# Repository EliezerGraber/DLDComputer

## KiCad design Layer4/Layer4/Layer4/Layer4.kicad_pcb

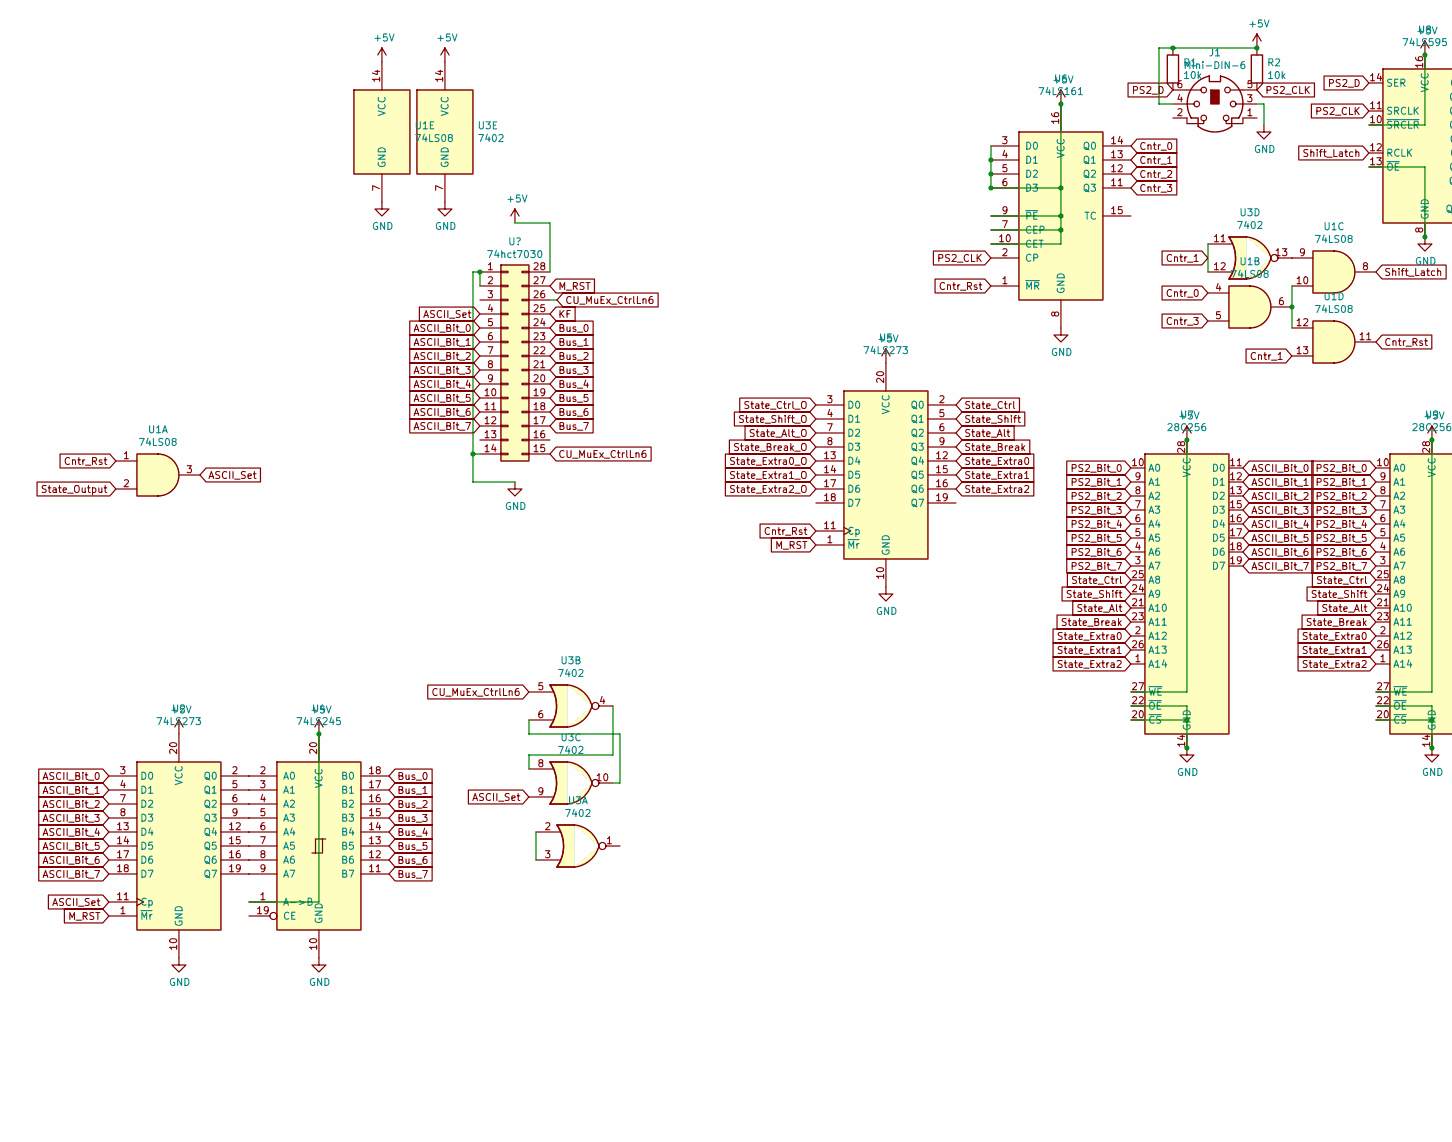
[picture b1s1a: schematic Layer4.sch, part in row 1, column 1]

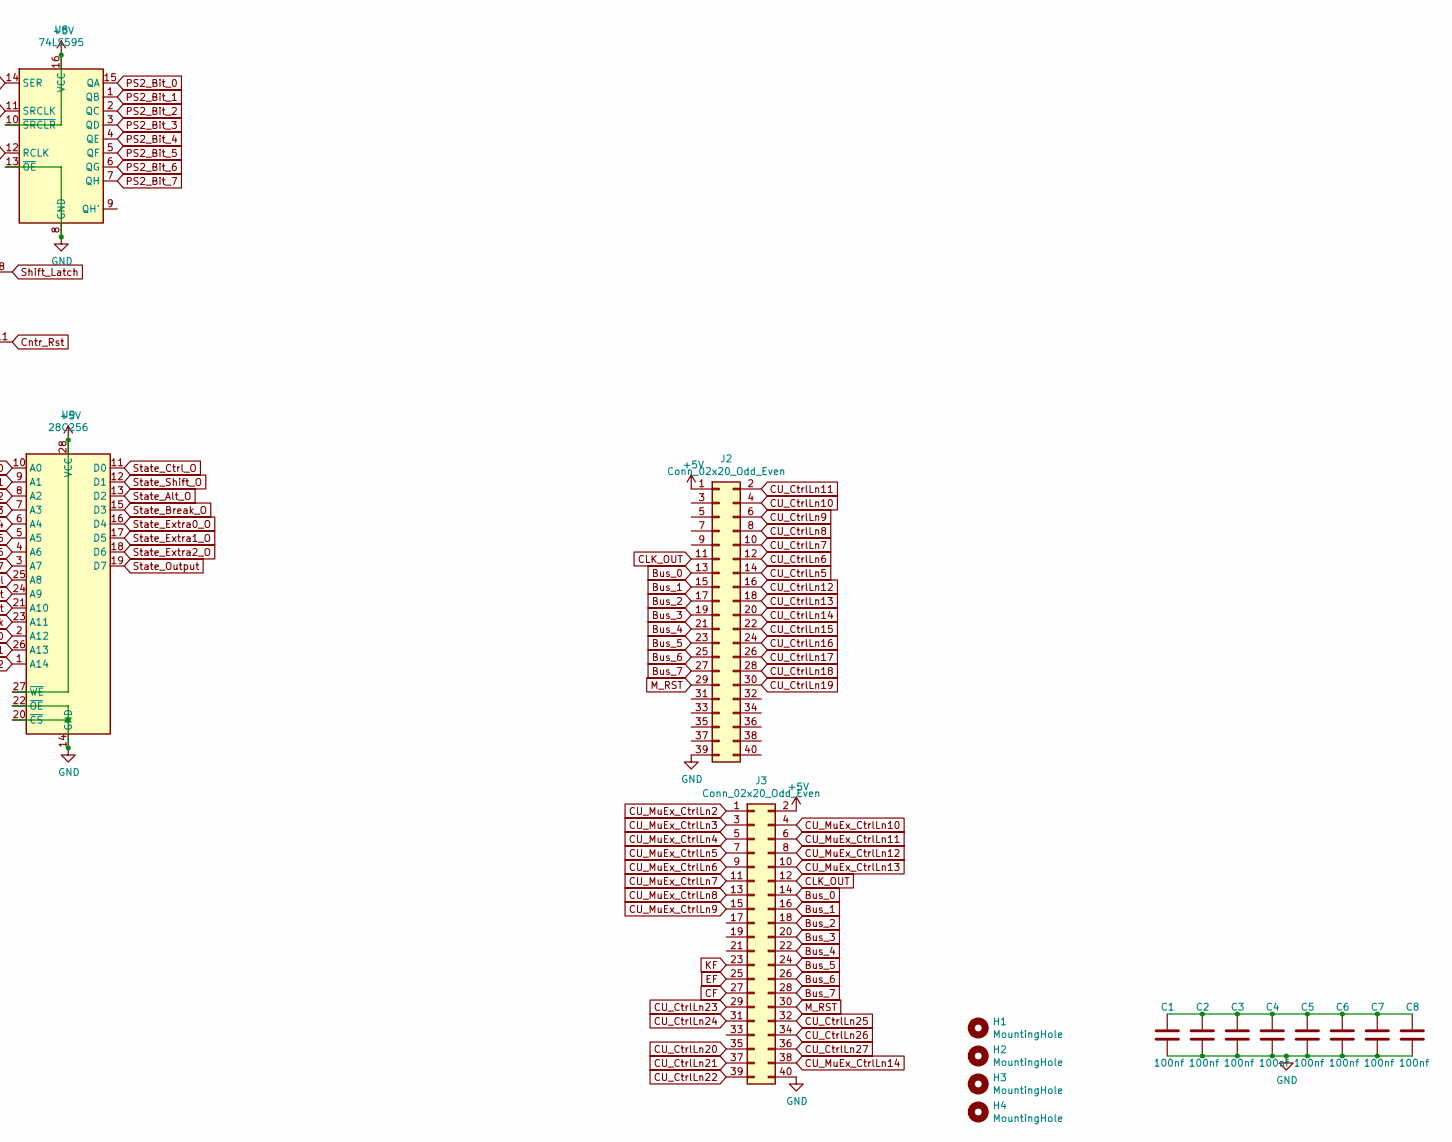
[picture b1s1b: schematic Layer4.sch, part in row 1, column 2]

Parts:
C1, C2, C3, C4, C5, C6, C7, C8: 100nf; C_Disc_D5.0mm_W2.5mm_P2.50mm
H1, H2, H3, H4: MountingHole; MountingHole_4mm
J1: Mini-DIN-6; Connector_Mini-DIN_Female_6Pin_2rows
J2, J3: Conn_02x20_Odd_Even; PinHeader_2x20_P2.54mm_Vertical
R1, R2: 10k; R_Axial_DIN0309_L9.0mm_D3.2mm_P12.70mm_Horizontal
U1: 74LS08; DIP-14_W7.62mm_LongPads
U2, U5: 74LS273; DIP-20_W7.62mm_LongPads
U3: 7402; DIP-14_W7.62mm_LongPads
U4: 74LS245; DIP-20_W7.62mm_LongPads
U6: 74LS161; DIP-16_W7.62mm_LongPads
U7, U9: 28C256; DIP-28_W15.24mm_LongPads
U8: 74LS595; DIP-16_W7.62mm_LongPads

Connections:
+5V: J1.4, J2.1, J3.2, R1.1, R2.1, U1.14 (VCC), U2.20 (VCC), U3.14 (VCC), U4.1 (A->B), U4.20 (VCC), U5.20 (VCC), U6.3 (D0), U6.4 (D1), U6.5 (D2), U6.6 (D3), U6.7 (CEP), U6.9 (~PE), U6.10 (CET), U6.16 (VCC), U7.27 (~WE), U7.28 (VCC), U8.10 (~SRCLR), U8.16 (VCC), U9.27 (~WE), U9.28 (VCC)
ASCII_Bit_0: U2.3 (D0), U7.11 (D0)
ASCII_Bit_1: U2.4 (D1), U7.12 (D1)
ASCII_Bit_2: U2.7 (D2), U7.13 (D2)
ASCII_Bit_3: U2.8 (D3), U7.15 (D3)
ASCII_Bit_4: U2.13 (D4), U7.16 (D4)
ASCII_Bit_5: U2.14 (D5), U7.17 (D5)
ASCII_Bit_6: U2.17 (D6), U7.18 (D6)
ASCII_Bit_7: U2.18 (D7), U7.19 (D7)
ASCII_Set: U1.3, U2.11 (Cp), U3.9
Bus_0: J2.13, J3.14, U4.18 (B0)
Bus_1: J2.15, J3.16, U4.17 (B1)
Bus_2: J2.17, J3.18, U4.16 (B2)
Bus_3: J2.19, J3.20, U4.15 (B3)
Bus_4: J2.21, J3.22, U4.14 (B4)
Bus_5: J2.23, J3.24, U4.13 (B5)
Bus_6: J2.25, J3.26, U4.12 (B6)
Bus_7: J2.27, J3.28, U4.11 (B7)
CF: J3.27
CLK_OUT: J2.11, J3.12
CU_CtrlLn5: J2.14
CU_CtrlLn6: J2.12
CU_CtrlLn7: J2.10
CU_CtrlLn8: J2.8
CU_CtrlLn9: J2.6
CU_CtrlLn10: J2.4
CU_CtrlLn11: J2.2
CU_CtrlLn12: J2.16
CU_CtrlLn13: J2.18
CU_CtrlLn14: J2.20
CU_CtrlLn15: J2.22
CU_CtrlLn16: J2.24
CU_CtrlLn17: J2.26
CU_CtrlLn18: J2.28
CU_CtrlLn19: J2.30
CU_CtrlLn20: J3.35
CU_CtrlLn21: J3.37
CU_CtrlLn22: J3.39
CU_CtrlLn23: J3.29
CU_CtrlLn24: J3.31
CU_CtrlLn25: J3.32
CU_CtrlLn26: J3.34
CU_CtrlLn27: J3.36
CU_MuEx_CtrlLn2: J3.1
CU_MuEx_CtrlLn3: J3.3
CU_MuEx_CtrlLn4: J3.5
CU_MuEx_CtrlLn5: J3.7
CU_MuEx_CtrlLn7: J3.11
CU_MuEx_CtrlLn8: J3.13
CU_MuEx_CtrlLn9: J3.15
CU_MuEx_CtrlLn10: J3.4
CU_MuEx_CtrlLn11: J3.6
CU_MuEx_CtrlLn12: J3.8
CU_MuEx_CtrlLn13: J3.10
CU_MuEx_CtrlLn14: J3.38
Cntr_0: U1.4, U6.14 (Q0)
Cntr_1: U1.13, U3.11, U3.12, U6.13 (Q1)
Cntr_2: U6.12 (Q2)
Cntr_3: U1.5, U6.11 (Q3)
Cntr_Rst: U1.1, U1.11, U5.11 (Cp), U6.1 (~MR)
EF: J3.25
GND: C1.2, C2.2, C3.2, C4.2, C5.2, C6.2, C7.2, C8.2, J1.3, J2.39, J3.40, U1.7 (GND), U2.10 (GND), U3.7 (GND), U4.10 (GND), U5.10 (GND), U6.8 (GND), U7.14 (GND), U7.20 (~CS), U7.22 (~OE), U8.8 (GND), U8.13 (~OE), U9.14 (GND), U9.20 (~CS), U9.22 (~OE)
M_RST: J2.29, J3.30, U2.1 (~Mr), U5.1 (~Mr)
unnamed: C1.1, C2.1, C3.1, C4.1, C5.1, C6.1, C7.1, C8.1
unnamed: U1.9, U3.13
unnamed: U1.6, U1.10, U1.12
unnamed: U2.2 (Q0), U4.2 (A0)
unnamed: U2.5 (Q1), U4.3 (A1)
unnamed: U2.6 (Q2), U4.4 (A2)
unnamed: U2.9 (Q3), U4.5 (A3)
unnamed: U2.12 (Q4), U4.6 (A4)
unnamed: U2.15 (Q5), U4.7 (A5)
unnamed: U2.16 (Q6), U4.8 (A6)
unnamed: U2.19 (Q7), U4.9 (A7)
unnamed: U3.1, U4.19 (CE)
unnamed: U3.6, U3.10
PS2_Bit_0: U7.10 (A0), U8.15 (QA), U9.10 (A0)
PS2_Bit_1: U7.9 (A1), U8.1 (QB), U9.9 (A1)
PS2_Bit_2: U7.8 (A2), U8.2 (QC), U9.8 (A2)
PS2_Bit_3: U7.7 (A3), U8.3 (QD), U9.7 (A3)
PS2_Bit_4: U7.6 (A4), U8.4 (QE), U9.6 (A4)
PS2_Bit_5: U7.5 (A5), U8.5 (QF), U9.5 (A5)
PS2_Bit_6: U7.4 (A6), U8.6 (QG), U9.4 (A6)
PS2_Bit_7: U7.3 (A7), U8.7 (QH), U9.3 (A7)
PS2_CLK: J1.5, R2.2, U6.2 (CP), U8.11 (SRCLK)
PS2_D: J1.6, R1.2, U8.14 (SER)
Shift_Latch: U1.8, U8.12 (RCLK)
State_Alt: U5.6 (Q2), U7.21 (A10), U9.21 (A10)
State_Alt_O: U5.7 (D2), U9.13 (D2)
State_Break: U5.9 (Q3), U7.23 (A11), U9.23 (A11)
State_Break_O: U5.8 (D3), U9.15 (D3)
State_Ctrl: U5.2 (Q0), U7.25 (A8), U9.25 (A8)
State_Ctrl_O: U5.3 (D0), U9.11 (D0)
State_Extra0: U5.12 (Q4), U7.2 (A12), U9.2 (A12)
State_Extra0_O: U5.13 (D4), U9.16 (D4)
State_Extra1: U5.15 (Q5), U7.26 (A13), U9.26 (A13)
State_Extra1_O: U5.14 (D5), U9.17 (D5)
State_Extra2: U5.16 (Q6), U7.1 (A14), U9.1 (A14)
State_Extra2_O: U5.17 (D6), U9.18 (D6)
State_Output: U1.2, U9.19 (D7)
State_Shift: U5.5 (Q1), U7.24 (A9), U9.24 (A9)
State_Shift_O: U5.4 (D1), U9.12 (D1)

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
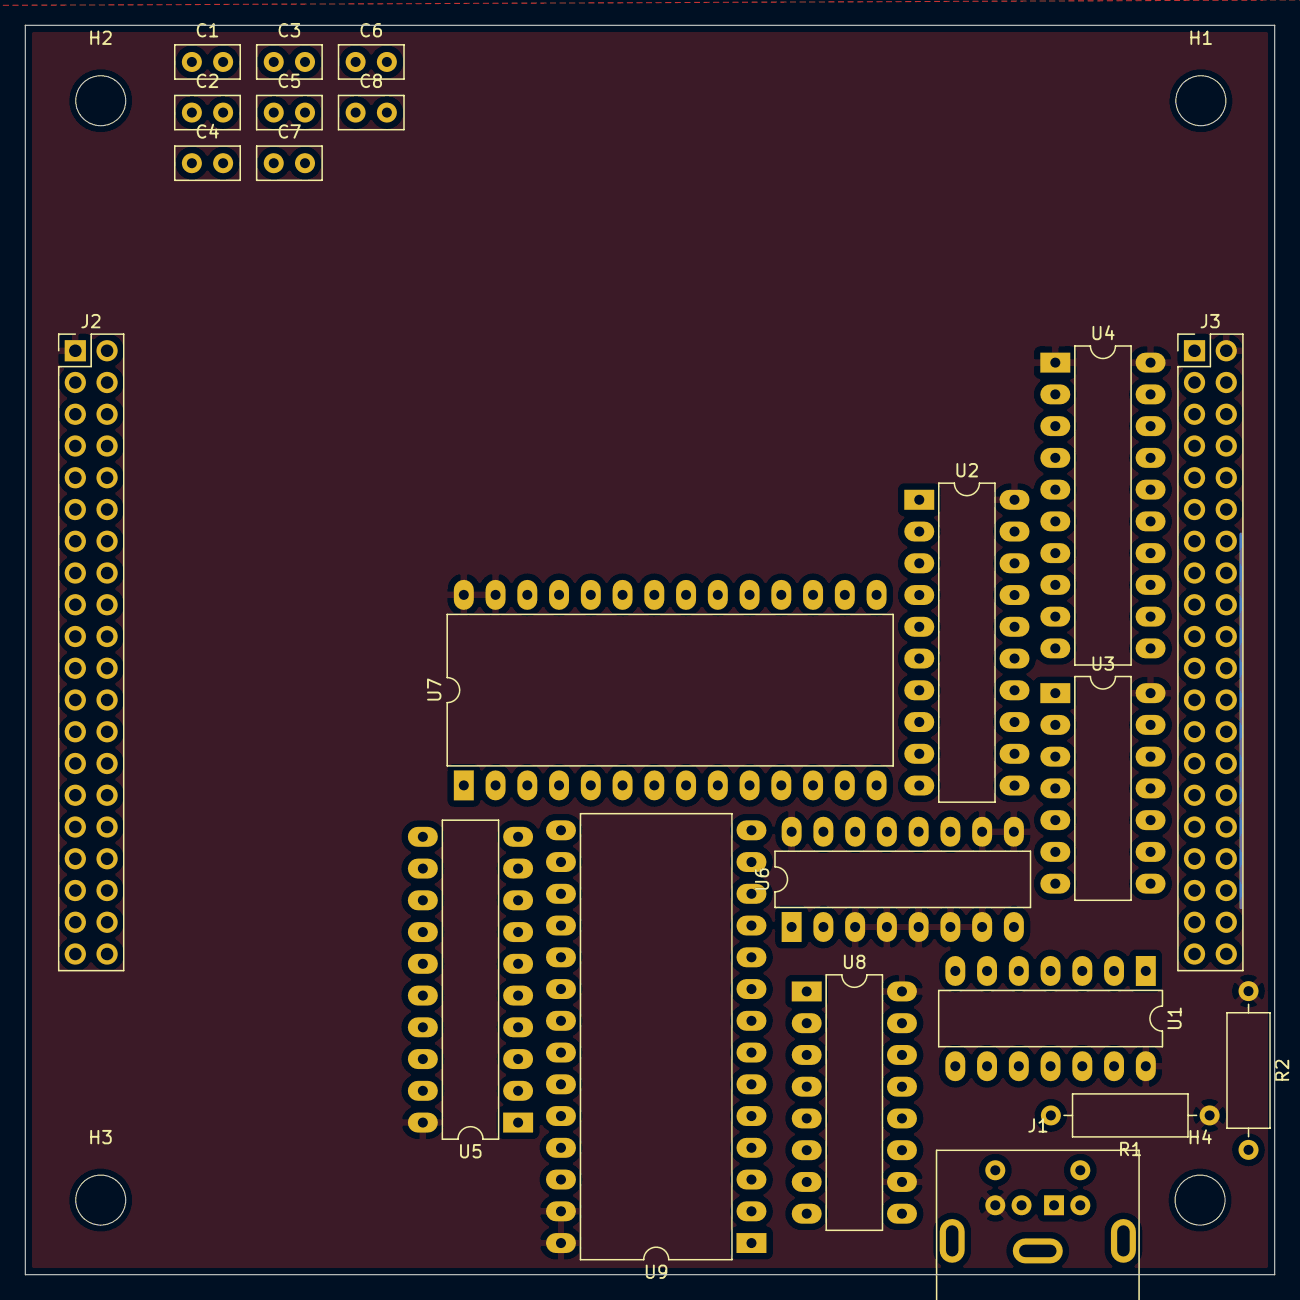
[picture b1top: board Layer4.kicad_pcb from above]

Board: 2 copper layers, 99.9 x 99.9 mm, 26 parts (0 on the bottom side), 66 nets.

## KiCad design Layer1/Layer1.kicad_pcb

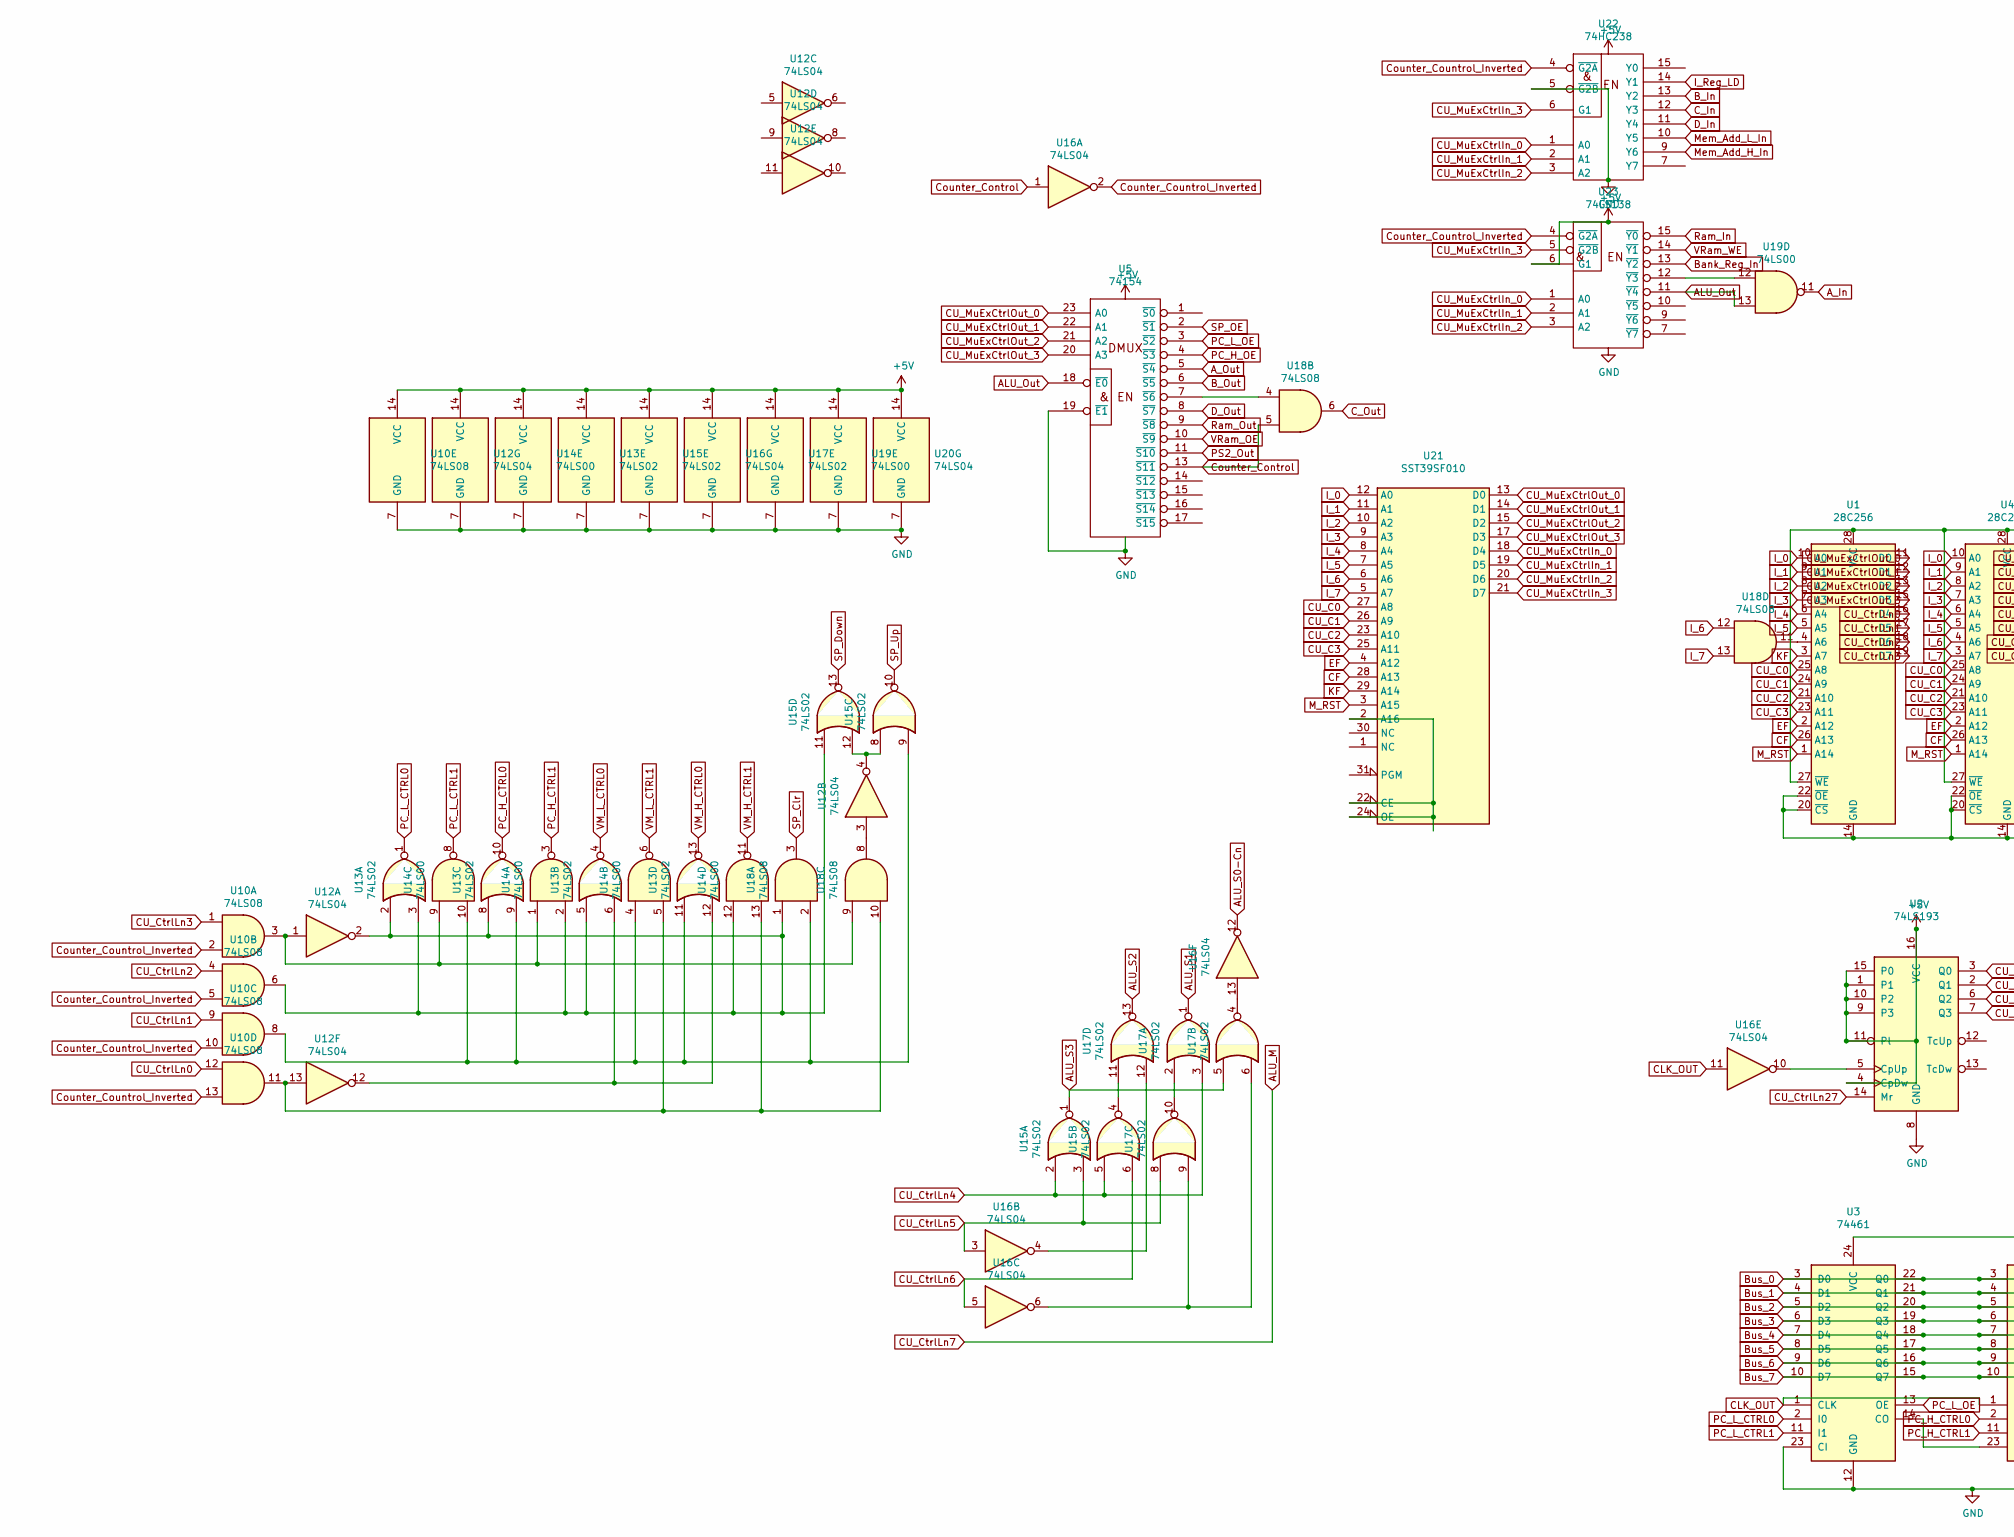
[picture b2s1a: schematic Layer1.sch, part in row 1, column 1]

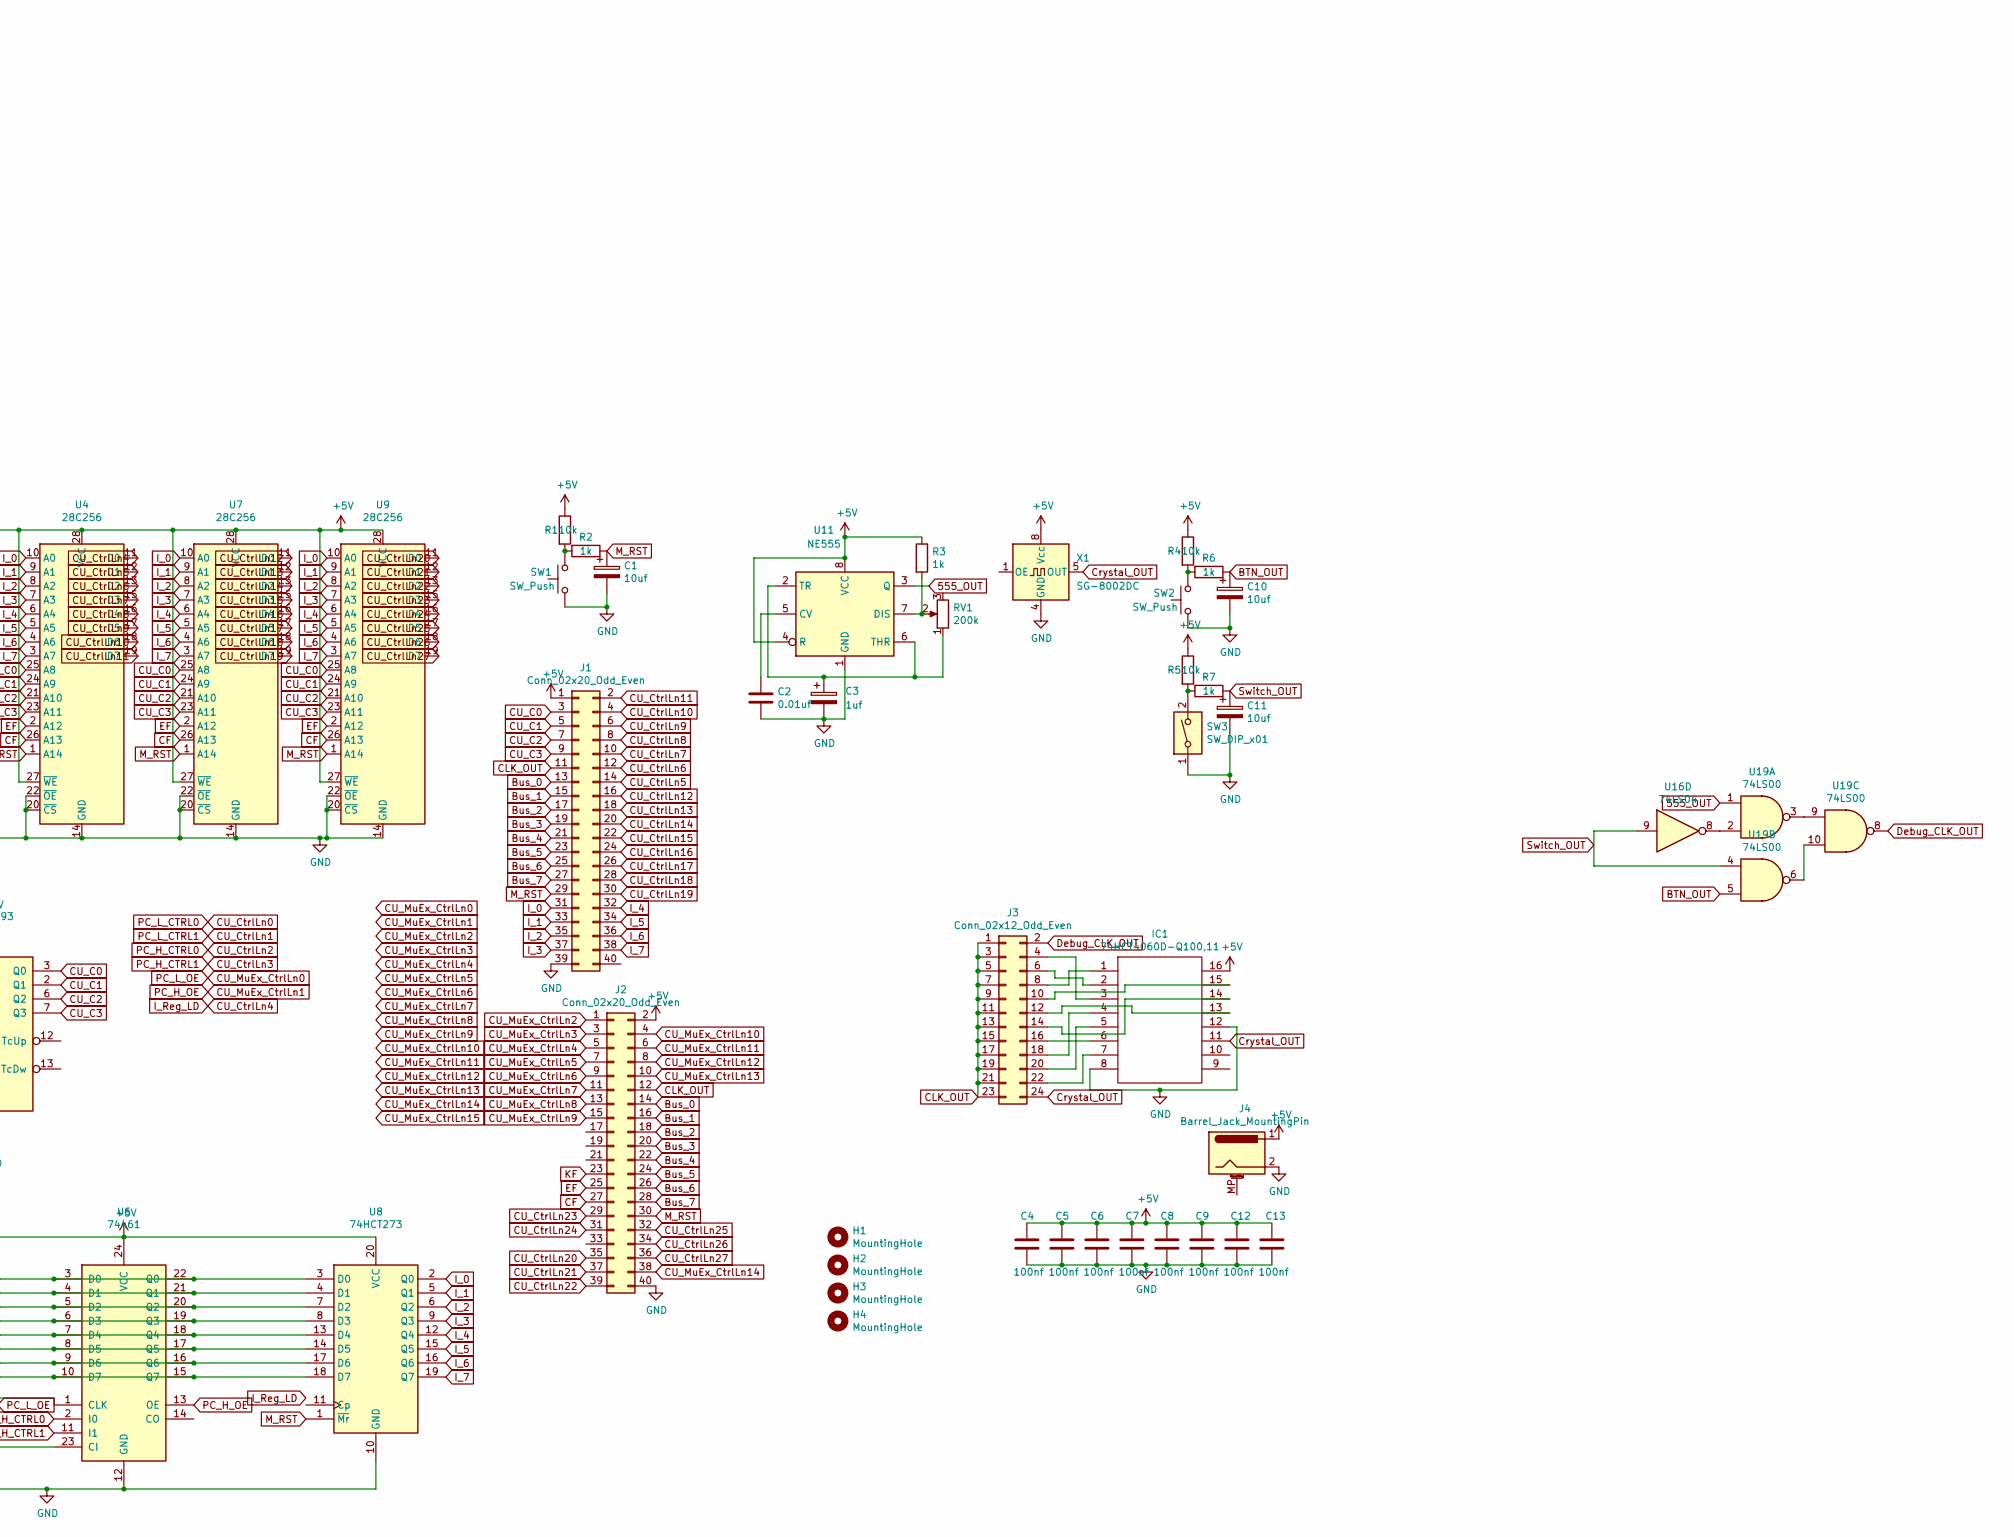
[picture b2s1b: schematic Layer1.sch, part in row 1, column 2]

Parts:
C1, C10, C11: 10uf; CP_Radial_D5.0mm_P2.00mm
C2: 0.01uf; C_Disc_D5.0mm_W2.5mm_P2.50mm
C3: 1uf; CP_Radial_D5.0mm_P2.00mm
C4, C5, C6, C7, C8, C9, C12, C13: 100nf; C_Disc_D5.0mm_W2.5mm_P2.50mm
H1, H2, H3, H4: MountingHole; MountingHole_4mm
IC1: 74HCT4060D-Q100,11; DIP-16_W7.62mm_LongPads; Manufacturer_Part_Number 74HCT4060D-Q100,11; Mouser Part Number 771-74HCT4060DQ10011
J1, J2: Conn_02x20_Odd_Even; PinHeader_2x20_P2.54mm_Vertical
J3: Conn_02x12_Odd_Even; PinHeader_2x12_P2.54mm_Vertical
J4: Barrel_Jack_MountingPin; BarrelJack_CUI_PJ-102AH_Horizontal
R1, R4, R5: 10k; R_Axial_DIN0309_L9.0mm_D3.2mm_P12.70mm_Horizontal
R2, R3, R6, R7: 1k; R_Axial_DIN0309_L9.0mm_D3.2mm_P12.70mm_Horizontal
RV1: 200k; Potentiometer_Bourns_3386P_Vertical
SW1, SW2: SW_Push; SW_PUSH_6mm
SW3: SW_DIP_x01; SW_DIP_SPSTx01_Slide_9.78x4.72mm_W7.62mm_P2.54mm
U1, U4, U7, U9: 28C256; DIP-28_W15.24mm_LongPads
U2: 74LS193; DIP-16_W7.62mm_LongPads
U3, U6: 74461; DIP-24_W7.62mm_LongPads
U5: 74154; DIP-24_W7.62mm_LongPads
U8: 74HCT273; DIP-20_W7.62mm_LongPads
U10, U18: 74LS08; DIP-14_W7.62mm_LongPads
U11: NE555; DIP-8_W7.62mm_Socket_LongPads
U12, U16, U20: 74LS04; DIP-14_W7.62mm_LongPads
U13, U15, U17: 74LS02; DIP-14_W7.62mm_LongPads
U14, U19: 74LS00; DIP-14_W7.62mm_LongPads
U21: SST39SF010; DIP-32_W15.24mm_LongPads
U22: 74HC238; DIP-16_W7.62mm_LongPads
U23: 74LS138; DIP-16_W7.62mm_LongPads
X1: SG-8002DC; Oscillator_DIP-8

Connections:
555_OUT: U11.3 (Q), U19.1; also elsewhere on the board
+5V: C4.1, C5.1, C6.1, C7.1, C8.1, C9.1, C12.1, C13.1, IC1.16, J1.1, J2.2, J4.1, R1.1, R3.1, R4.1, R5.1, U1.27 (~WE), U1.28 (VCC), U2.1, U2.4 (CpDw), U2.9 (P3), U2.10 (P2), U2.11 (Pl), U2.15 (P0), U2.16 (VCC), U3.24 (VCC), U4.27 (~WE), U4.28 (VCC), U5.24 (VCC), U6.24 (VCC), U7.27 (~WE), U7.28 (VCC), U8.20 (VCC), U9.27 (~WE), U9.28 (VCC), U10.14 (VCC), U11.4 (R), U11.8 (VCC), U12.14 (VCC), U13.14 (VCC), U14.14 (VCC), U15.14 (VCC), U16.14 (VCC), U17.14 (VCC), U19.14 (VCC), U20.14 (VCC), U21.32 (VCC), U22.16 (VCC), U23.6 (G1), U23.16 (VCC), X1.8 (Vcc); also elsewhere on the board
ALU_M: J1.10, U4.15 (D3)
ALU_Out: U5.18 (~E0), U19.13, U23.11 (~Y4)
ALU_S0-Cn: U16.12
ALU_S1: U17.1
ALU_S2: U17.13
ALU_S3: U15.1, U17.5
A_In: U19.11
A_Out: U5.5 (~S4)
BTN_OUT: C10.1, R6.1, U19.5; also elsewhere on the board
B_In: U22.13 (Y2)
B_Out: U5.6 (~S5)
Bank_Reg_In: U23.13 (~Y2)
Bus_0: J1.13, J2.14, U3.3 (D0), U3.22 (Q0), U6.3 (D0), U6.22 (Q0), U8.3 (D0)
Bus_1: J1.15, J2.16, U3.4 (D1), U3.21 (Q1), U6.4 (D1), U6.21 (Q1), U8.4 (D1)
Bus_2: J1.17, J2.18, U3.5 (D2), U3.20 (Q2), U6.5 (D2), U6.20 (Q2), U8.7 (D2)
Bus_3: J1.19, J2.20, U3.6 (D3), U3.19 (Q3), U6.6 (D3), U6.19 (Q3), U8.8 (D3)
Bus_4: J1.21, J2.22, U3.7 (D4), U3.18 (Q4), U6.7 (D4), U6.18 (Q4), U8.13 (D4)
Bus_5: J1.23, J2.24, U3.8 (D5), U3.17 (Q5), U6.8 (D5), U6.17 (Q5), U8.14 (D5)
Bus_6: J1.25, J2.26, U3.9 (D6), U3.16 (Q6), U6.9 (D6), U6.16 (Q6), U8.17 (D6)
Bus_7: J1.27, J2.28, U3.10 (D7), U3.15 (Q7), U6.10 (D7), U6.15 (Q7), U8.18 (D7)
CF: J2.27, U1.26 (A13), U4.26 (A13), U7.26 (A13), U9.26 (A13), U21.28 (A13)
CLK_OUT: J1.11, J2.12, J3.1, J3.3, J3.5, J3.7, J3.9, J3.11, J3.13, J3.15, J3.17, J3.19, J3.21, J3.23, U3.1 (CLK), U6.1 (CLK), U16.11; also elsewhere on the board
CU_C0: J1.3, U1.25 (A8), U2.3 (Q0), U4.25 (A8), U7.25 (A8), U9.25 (A8), U21.27 (A8)
CU_C1: J1.5, U1.24 (A9), U2.2 (Q1), U4.24 (A9), U7.24 (A9), U9.24 (A9), U21.26 (A9)
CU_C2: J1.7, U1.21 (A10), U2.6 (Q2), U4.21 (A10), U7.21 (A10), U9.21 (A10), U21.23 (A10)
CU_C3: J1.9, U1.23 (A11), U2.7 (Q3), U4.23 (A11), U7.23 (A11), U9.23 (A11), U21.25 (A11)
CU_CtrlLn5: J1.14, U4.12 (D1), U15.3, U16.3, U17.8
CU_CtrlLn6: J1.12, U4.13 (D2), U15.6, U16.5
CU_CtrlLn8: J1.8, U4.16 (D4)
CU_CtrlLn9: J1.6, U4.17 (D5)
CU_CtrlLn10: J1.4, U4.18 (D6)
CU_CtrlLn11: J1.2, U4.19 (D7)
CU_CtrlLn12: J1.16, U7.11 (D0)
CU_CtrlLn13: J1.18, U7.12 (D1)
CU_CtrlLn14: J1.20, U7.13 (D2)
CU_CtrlLn15: J1.22, U7.15 (D3)
CU_CtrlLn16: J1.24, U7.16 (D4)
CU_CtrlLn17: J1.26, U7.17 (D5)
CU_CtrlLn18: J1.28, U7.18 (D6)
CU_CtrlLn19: J1.30, U7.19 (D7)
CU_CtrlLn20: J2.35, U9.11 (D0)
CU_CtrlLn21: J2.37, U9.12 (D1)
CU_CtrlLn22: J2.39, U9.13 (D2)
CU_CtrlLn23: J2.29, U9.15 (D3)
CU_CtrlLn24: J2.31, U9.16 (D4)
CU_CtrlLn25: J2.32, U9.17 (D5)
CU_CtrlLn26: J2.34, U9.18 (D6)
CU_CtrlLn27: J2.36, U2.14 (Mr), U9.19 (D7)
CU_MuExCtrlIn_0: U21.18 (D4), U22.1 (A0), U23.1 (A0)
CU_MuExCtrlIn_1: U21.19 (D5), U22.2 (A1), U23.2 (A1)
CU_MuExCtrlIn_2: U21.20 (D6), U22.3 (A2), U23.3 (A2)
CU_MuExCtrlIn_3: U21.21 (D7), U22.6 (G1), U23.5 (~G2B)
CU_MuExCtrlOut_0: U1.11 (D0), U5.23 (A0), U21.13 (D0)
CU_MuExCtrlOut_1: U1.12 (D1), U5.22 (A1), U21.14 (D1)
CU_MuExCtrlOut_2: U1.13 (D2), U5.21 (A2), U21.15 (D2)
CU_MuExCtrlOut_3: U1.15 (D3), U5.20 (A3), U21.17 (D3)
CU_MuEx_CtrlLn2: J2.1
CU_MuEx_CtrlLn3: J2.3
CU_MuEx_CtrlLn4: J2.5
CU_MuEx_CtrlLn5: J2.7
CU_MuEx_CtrlLn6: J2.9
CU_MuEx_CtrlLn7: J2.11
CU_MuEx_CtrlLn8: J2.13
CU_MuEx_CtrlLn9: J2.15
CU_MuEx_CtrlLn10: J2.4
CU_MuEx_CtrlLn11: J2.6
CU_MuEx_CtrlLn12: J2.8
CU_MuEx_CtrlLn13: J2.10
CU_MuEx_CtrlLn14: J2.38
C_In: U22.12 (Y3)
C_Out: U18.6
Counter_Control: U5.13 (~S11), U16.1, U18.5
Counter_Countrol_Inverted: U10.2, U10.5, U10.10, U10.13, U16.2, U22.4 (~G2A), U23.4 (~G2A)
Crystal_OUT: IC1.11, J3.24, X1.5 (OUT)
D_In: U22.11 (Y4)
D_Out: U5.8 (~S7)
Debug_CLK_OUT: J3.2, U19.8; also elsewhere on the board
EF: J2.25, U1.2 (A12), U4.2 (A12), U7.2 (A12), U9.2 (A12), U21.4 (A12)
I_0: J1.31, U1.10 (A0), U4.10 (A0), U7.10 (A0), U8.2 (Q0), U9.10 (A0), U21.12 (A0)
I_1: J1.33, U1.9 (A1), U4.9 (A1), U7.9 (A1), U8.5 (Q1), U9.9 (A1), U21.11 (A1)
I_2: J1.35, U1.8 (A2), U4.8 (A2), U7.8 (A2), U8.6 (Q2), U9.8 (A2), U21.10 (A2)
I_3: J1.37, U1.7 (A3), U4.7 (A3), U7.7 (A3), U8.9 (Q3), U9.7 (A3), U21.9 (A3)
I_4: J1.32, U1.6 (A4), U4.6 (A4), U7.6 (A4), U8.12 (Q4), U9.6 (A4), U21.8 (A4)
I_5: J1.34, U1.5 (A5), U4.5 (A5), U7.5 (A5), U8.15 (Q5), U9.5 (A5), U21.7 (A5)
I_6: J1.36, U4.4 (A6), U7.4 (A6), U8.16 (Q6), U9.4 (A6), U18.12, U21.6 (A6); also elsewhere on the board
I_7: J1.38, U4.3 (A7), U7.3 (A7), U8.19 (Q7), U9.3 (A7), U18.13, U21.5 (A7); also elsewhere on the board
KF: J2.23, U1.3 (A7), U21.29 (A14)
M_RST: C1.1, J1.29, J2.30, R2.1, U1.1 (A14), U4.1 (A14), U7.1 (A14), U8.1 (~Mr), U9.1 (A14), U21.3 (A15)
Mem_Add_H_In: U22.9 (Y6)
Mem_Add_L_In: U22.10 (Y5)
unnamed: C2.1, U11.5 (CV)
unnamed: C3.1, RV1.1, U11.2 (TR), U11.6 (THR)
unnamed: IC1.1, J3.8
unnamed: IC1.2, J3.6
unnamed: IC1.3, J3.4
unnamed: IC1.4, J3.18
unnamed: IC1.5, J3.20
unnamed: IC1.6, J3.16
unnamed: IC1.7, J3.22
unnamed: IC1.13, J3.12
unnamed: IC1.14, J3.14
unnamed: IC1.15, J3.10
unnamed: R1.2, R2.2, SW1.2
unnamed: R3.2, RV1.2, U11.7 (DIS)
unnamed: R4.2, R6.2, SW2.2
unnamed: R5.2, R7.2, SW3.2
unnamed 116: U1.4 (A6), U18.11; also elsewhere on the board
unnamed: U3.14 (CO), U6.23 (CI)
unnamed: U10.3, U12.1, U14.1, U14.9, U18.9
unnamed: U10.6, U12.2, U13.2, U13.3, U13.5, U13.8, U14.2, U14.12, U15.11, U18.1
unnamed: U10.8, U13.9, U13.11, U14.4, U14.10, U15.9, U18.2
unnamed: U10.11, U12.13, U14.5, U14.13, U18.10
unnamed 131: U12.3, U18.8; also elsewhere on the board
unnamed: U12.4, U15.8, U15.12
unnamed 134: U12.6; also elsewhere on the board
unnamed 139: U12.12, U13.6, U13.12; also elsewhere on the board
unnamed: U15.4, U17.11
unnamed: U16.4, U17.12
unnamed: U16.6, U17.6, U17.9
unnamed: U16.8, U19.2
unnamed: U2.5 (CpUp), U16.10
unnamed: U16.13, U17.4
unnamed: U17.2, U17.10
unnamed: U5.7 (~S6), U18.4
unnamed: U19.3, U19.9
unnamed: U19.6, U19.10
unnamed: U19.12, U23.12 (~Y3)
PC_H_OE: U5.4 (~S3), U6.13 (OE)
PC_L_OE: U3.13 (OE), U5.3 (~S2)
PS2_Out: U5.11 (~S10)
Ram_In: U23.15 (~Y0)
Ram_Out: U5.9 (~S8)
SP_Clr: U18.3
SP_Down: U15.13
SP_OE: U5.2 (~S1)
SP_Up: U15.10
Switch_OUT: C11.1, R7.1, U16.9, U19.4; also elsewhere on the board
VM_H_CTRL0: U13.13
VM_H_CTRL1: U14.11
VM_L_CTRL0: U13.4
VM_L_CTRL1: U14.6
VRam_OE: U5.10 (~S9)
VRam_WE: U23.14 (~Y1)

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
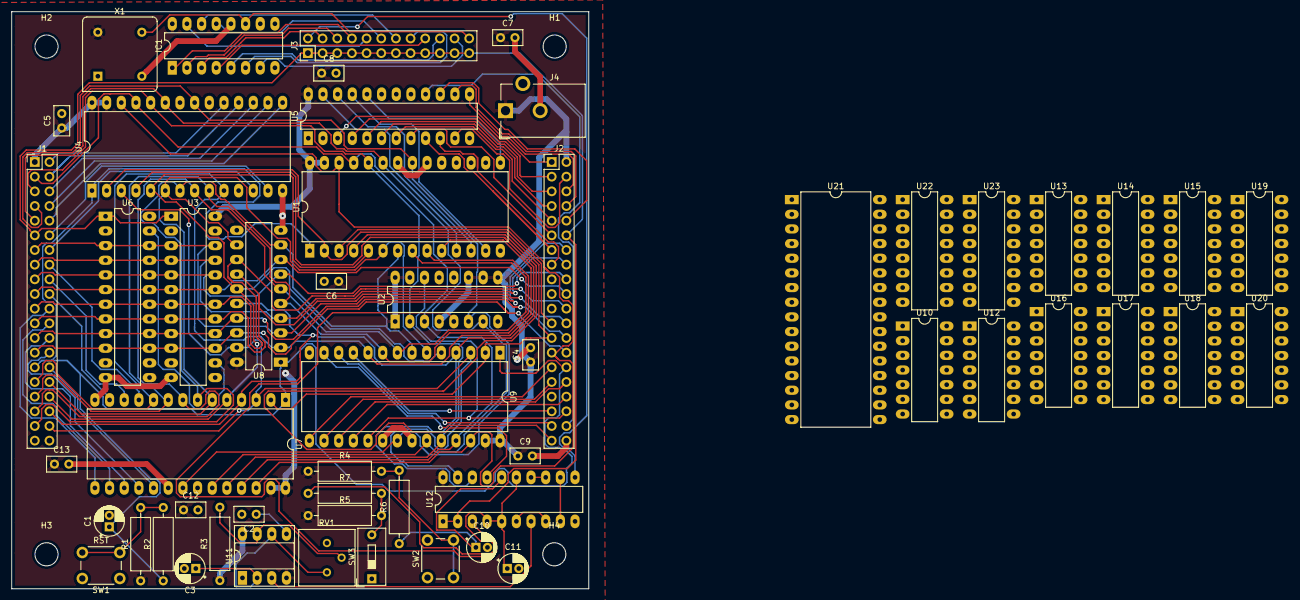
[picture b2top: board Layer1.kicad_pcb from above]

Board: 2 copper layers, 99.9 x 99.9 mm, 58 parts (0 on the bottom side), 116 nets.

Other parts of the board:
U12#2: 74HC804; DIP-20_W7.62mm_LongPads

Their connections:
555_OUT: U12#2.7; also elsewhere on the board
+5V: U12#2.20; also elsewhere on the board
BTN_OUT: U12#2.16; also elsewhere on the board
CLK_OUT: U12#2.1, U12#2.2; also elsewhere on the board
Debug_CLK_OUT: U12#2.11; also elsewhere on the board
I_6: U12#2.18; also elsewhere on the board
I_7: U12#2.19; also elsewhere on the board
unnamed 116: U12#2.17; also elsewhere on the board
unnamed 131: U12#2.3; also elsewhere on the board
unnamed 134: U12#2.6, U12#2.8; also elsewhere on the board
unnamed 139: U12#2.9, U12#2.12; also elsewhere on the board
unnamed: U12#2.13, U12#2.14
Switch_OUT: U12#2.4, U12#2.5, U12#2.15; also elsewhere on the board
